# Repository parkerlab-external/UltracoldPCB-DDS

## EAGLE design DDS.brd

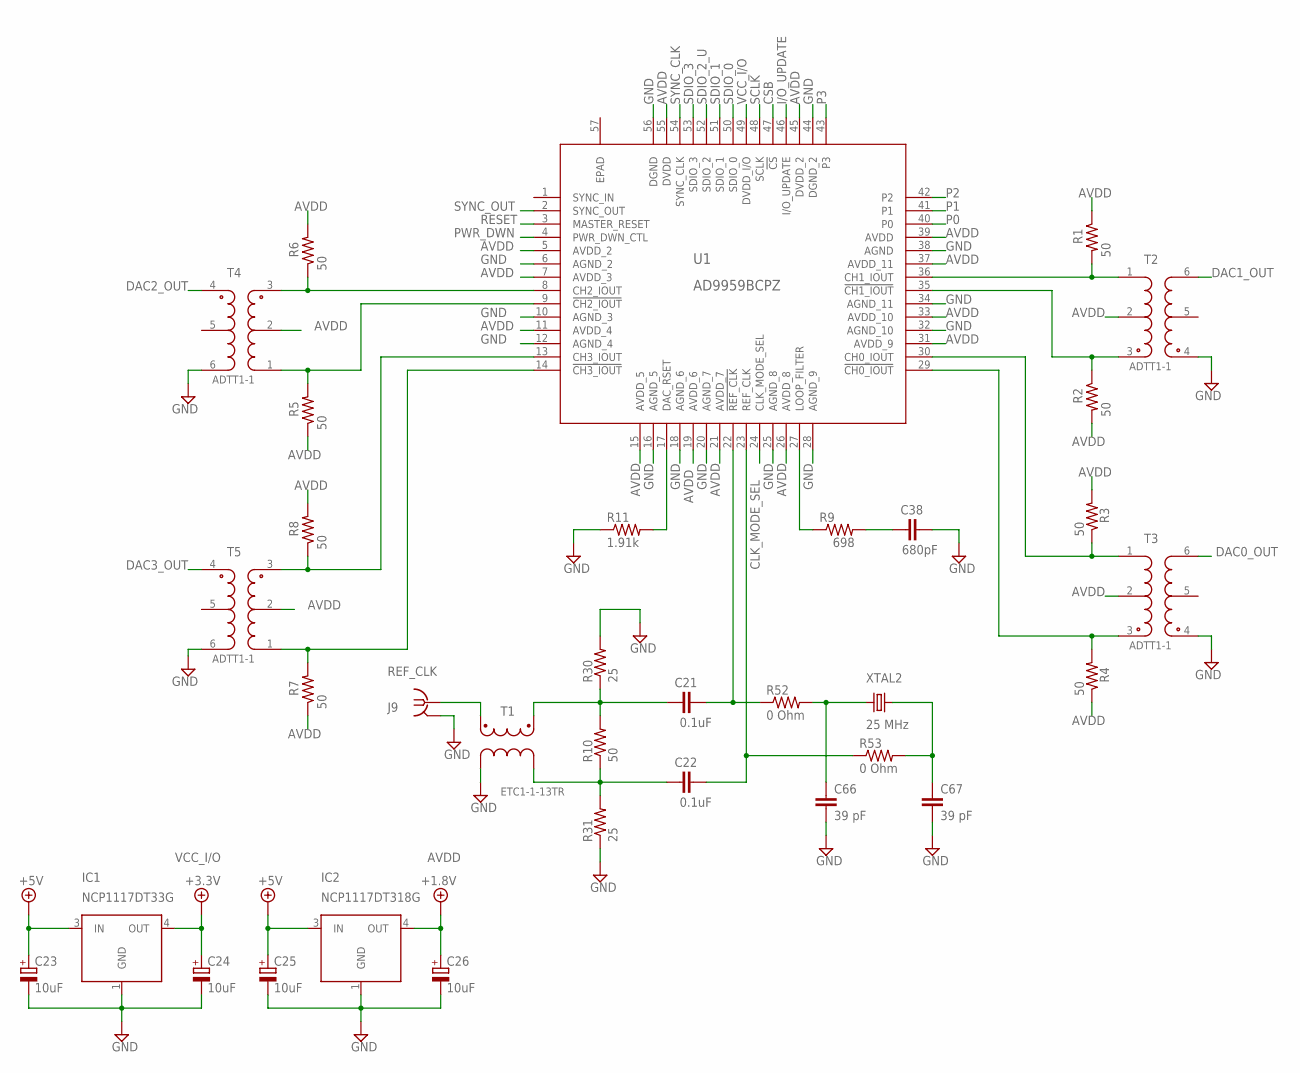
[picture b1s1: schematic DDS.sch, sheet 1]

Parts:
C21, C22: 0.1uF; C0402; MPN C0402C104K4RACTU
C23, C24, C25, C26: 10uF; CT3528; MPN T494B106K025AT
C38: 680pF; C0805; MPN MC0805N681J101CT
C66, C67: 39 pF; C0805; MPN MC0805N390J500CT
IC1: NCP1117DT33G; D-PAK_TO252AA; MPN NCP1117DT33G
IC2: NCP1117DT318G; D-PAK_TO252AA; MPN NCP1117DT18G
J9: REF_CLK; BU-SMA-V; MPN 142-0701-231
R1, R2, R3, R4, R5, R6, R7, R8, R10: 50; R0603; MPN CRCW060350R0FKEA
R9: 698; R0603; MPN ERJ-3EKF6980V
R11: 1.91k; R0603; MPN CRCW06031K91FKEA
R30, R31: 25; R0402; MPN NRC04F24R9TRF
R52, R53: 0 Ohm; R0402; MPN ERJ2GE0R00X
T1: ETC1-1-13TR; SM22
T2, T3, T4, T5: ADTT1-1; ADTT
U1: AD9959BCPZ; CP_56_1_ADI
XTAL2: 25 MHz; HC49UP

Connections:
+5V: C23.+, C25.+, IC1.3 (IN), IC2.3 (IN); also elsewhere on the board
AVDD: C26.+, IC2.4 (OUT), R1.1, R2.2, R3.2, R4.1, R5.1, R6.2, R7.1, R8.2, T2.2 (PRI0), T3.2 (PRI0), T4.2 (PRI0), T5.2 (PRI0), U1.5 (AVDD_2), U1.7 (AVDD_3), U1.11 (AVDD_4), U1.15 (AVDD_5), U1.19 (AVDD_6), U1.21 (AVDD_7), U1.26 (AVDD_8), U1.31 (AVDD_9), U1.33 (AVDD_10), U1.37 (AVDD_11), U1.39 (AVDD), U1.45 (DVDD_2), U1.55 (DVDD); also elsewhere on the board
CLK_MODE_SEL: U1.24 (CLK_MODE_SEL); also elsewhere on the board
CSB: U1.47 (!CS); also elsewhere on the board
DAC0_OUT: T3.6 (SEC-); also elsewhere on the board
DAC1_OUT: T2.6 (SEC-); also elsewhere on the board
DAC2_OUT: T4.4 (SEC+); also elsewhere on the board
DAC3_OUT: T5.4 (SEC+); also elsewhere on the board
GND: C23.-, C24.-, C25.-, C26.-, C38.2, C66.2, C67.2, IC1.1 (GND), IC2.1 (GND), J9.2 (GND), J9.3 (GND), J9.4 (GND), J9.5 (GND), R11.1, R30.2, R31.1, T1.4, T2.4 (SEC+), T3.4 (SEC+), T4.6 (SEC-), T5.6 (SEC-), U1.6 (AGND_2), U1.10 (AGND_3), U1.12 (AGND_4), U1.16 (AGND_5), U1.18 (AGND_6), U1.20 (AGND_7), U1.25 (AGND_8), U1.28 (AGND_9), U1.32 (AGND_10), U1.34 (AGND_11), U1.38 (AGND), U1.44 (DGND_2), U1.56 (DGND); also elsewhere on the board
I/O_UPDATE: U1.46 (I/O_UPDATE); also elsewhere on the board
unnamed: C21.1, R10.2, R30.1, T1.1
unnamed: R6.1, T4.3 (PRI+), U1.8 (CH2_IOUT)
unnamed: R5.2, T4.1 (PRI-), U1.9 (!CH2_IOUT)
unnamed: R4.2, T3.3 (PRI+), U1.29 (!CH0_IOUT)
unnamed: R1.2, T2.1 (PRI-), U1.36 (CH1_IOUT)
unnamed: R11.2, U1.17 (DAC_RSET)
unnamed: R9.1, U1.27 (LOOP_FILTER)
unnamed: C38.1, R9.2
unnamed: R7.2, T5.1 (PRI-), U1.14 (!CH3_IOUT)
unnamed: C66.1, R52.2, XTAL2.1
unnamed: R3.1, T3.1 (PRI-), U1.30 (CH0_IOUT)
unnamed: C67.1, R53.2, XTAL2.2
unnamed: C21.2, R52.1, U1.22 (!REF_CLK)
unnamed: C22.1, R10.1, R31.2, T1.3
unnamed: J9.1, T1.5
unnamed: C22.2, R53.1, U1.23 (REF_CLK)
unnamed: R8.1, T5.3 (PRI+), U1.13 (CH3_IOUT)
unnamed: R2.1, T2.3 (PRI+), U1.35 (!CH1_IOUT)
P0: U1.40 (P0); also elsewhere on the board
P1: U1.41 (P1); also elsewhere on the board
P2: U1.42 (P2); also elsewhere on the board
P3: U1.43 (P3); also elsewhere on the board
PWR_DWN: U1.4 (PWR_DWN_CTL); also elsewhere on the board
RESET: U1.3 (MASTER_RESET); also elsewhere on the board
SCLK: U1.48 (SCLK); also elsewhere on the board
SDIO_0: U1.50 (SDIO_0); also elsewhere on the board
SDIO_1: U1.51 (SDIO_1); also elsewhere on the board
SDIO_2_U: U1.52 (SDIO_2); also elsewhere on the board
SDIO_3: U1.53 (SDIO_3); also elsewhere on the board
SYNC_CLK: U1.54 (SYNC_CLK)
SYNC_OUT: U1.2 (SYNC_OUT)
VCC_I/O: C24.+, IC1.4 (OUT), U1.49 (DVDD_I/O); also elsewhere on the board

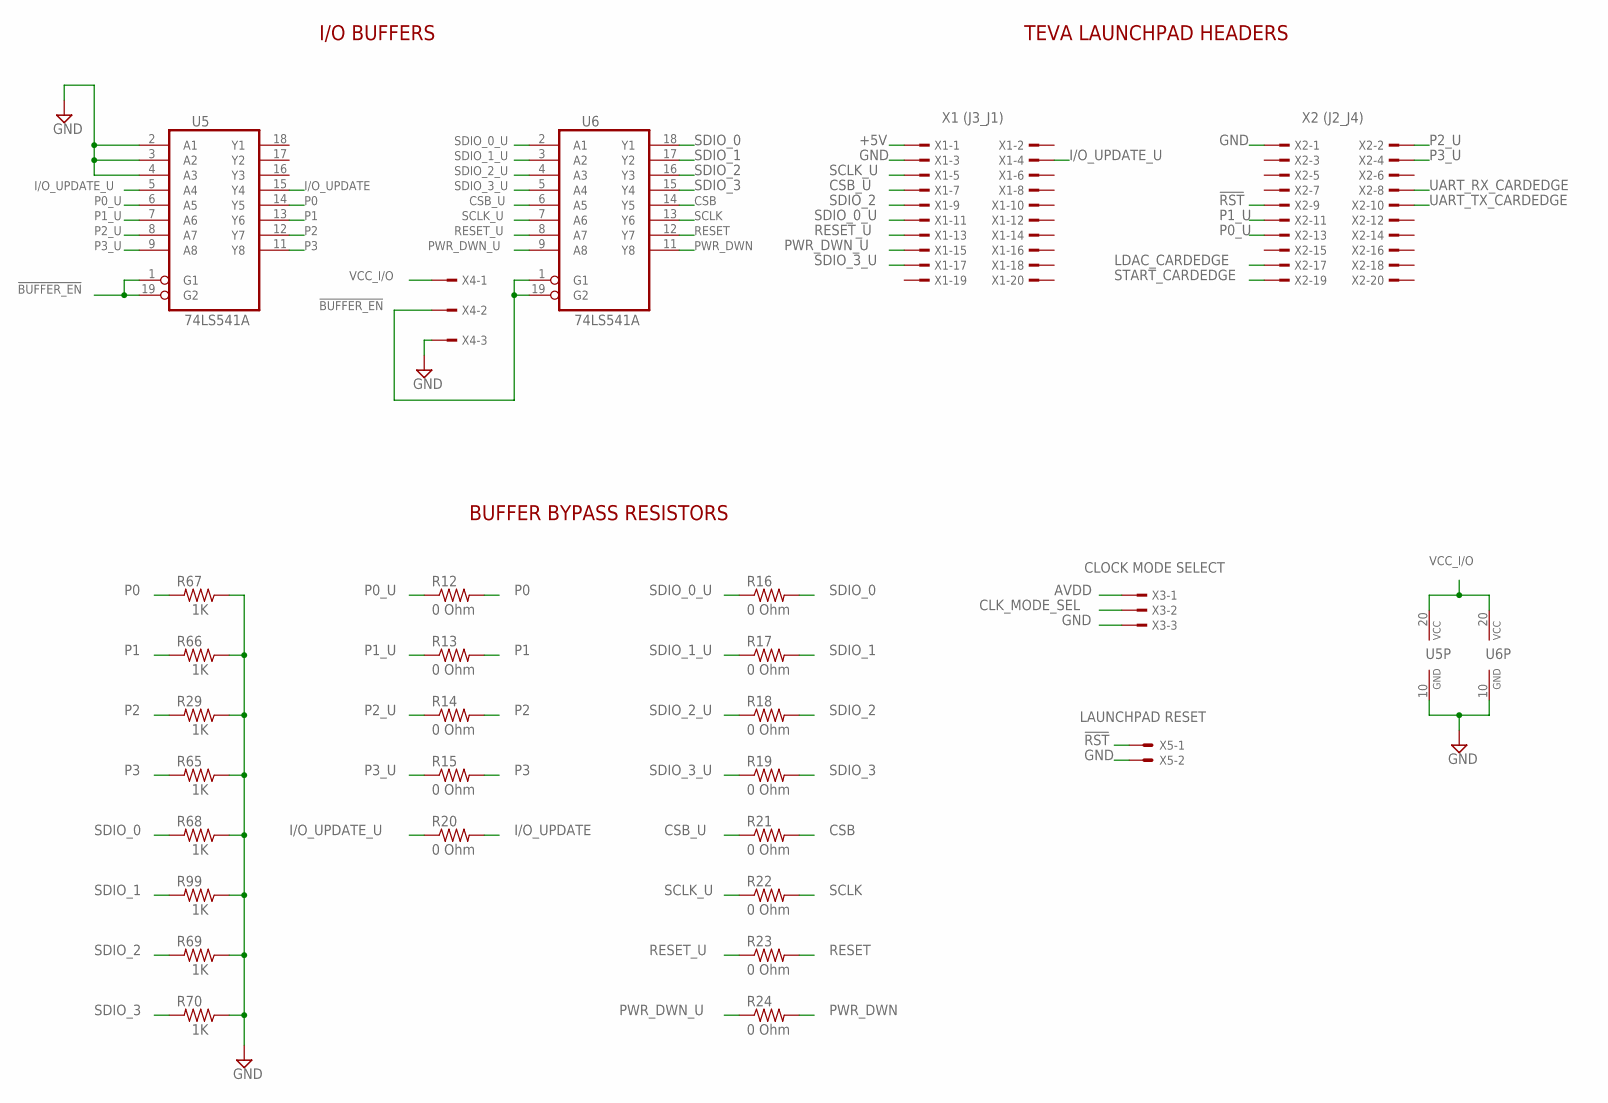
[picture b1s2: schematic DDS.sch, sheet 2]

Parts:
R12, R13, R14, R15, R16, R17, R18, R19, R20, R21, R22, R23, R24: 0 Ohm; R0402; MPN ERJ2GE0R00X
R29, R65, R66, R67, R68, R69, R70, R99: 1K; R0603; MPN ERJ-3EKF1001V
U5, U6: 74LS541A; SO20W; MPN SN74LVC541APW
X1: X1 (J3_J1); TSW-110-XX-G-D
X2: X2 (J2_J4); TSW-110-XX-G-D
X3: CLOCK MODE SELECT; TSW-103-XX-G-S
X4: BUFFER; TSW-103-XX-G-S
X5: LAUNCHPAD RESET; 22-23-2021

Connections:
!BUFFER_EN: U5.1 (G1), U5.19 (G2), U6.1 (G1), U6.19 (G2), X4.2
!RST: X2.9, X5.1
+5V: X1.1; also elsewhere on the board
AVDD: X3.1; also elsewhere on the board
CLK_MODE_SEL: X3.2; also elsewhere on the board
CSB: R21.2, U6.14 (Y5); also elsewhere on the board
CSB_U: R21.1, U6.6 (A5), X1.7
GND: R29.1, R65.1, R66.1, R67.1, R68.1, R69.1, R70.1, R99.1, U5.2 (A1), U5.3 (A2), U5.4 (A3), U5.10 (GND), U6.10 (GND), X1.3, X2.1, X3.3, X4.3, X5.2; also elsewhere on the board
I/O_UPDATE: R20.2, U5.15 (Y4); also elsewhere on the board
I/O_UPDATE_U: R20.1, U5.5 (A4), X1.4
LDAC_CARDEDGE: X2.17
P0: R12.2, R67.2, U5.14 (Y5); also elsewhere on the board
P0_U: R12.1, U5.6 (A5), X2.13
P1: R13.2, R66.2, U5.13 (Y6); also elsewhere on the board
P1_U: R13.1, U5.7 (A6), X2.11
P2: R14.2, R29.2, U5.12 (Y7); also elsewhere on the board
P2_U: R14.1, U5.8 (A7), X2.2
P3: R15.2, R65.2, U5.11 (Y8); also elsewhere on the board
P3_U: R15.1, U5.9 (A8), X2.4
PWR_DWN: R24.2, U6.11 (Y8); also elsewhere on the board
PWR_DWN_U: R24.1, U6.9 (A8), X1.15
RESET: R23.2, U6.12 (Y7); also elsewhere on the board
RESET_U: R23.1, U6.8 (A7), X1.13
SCLK: R22.2, U6.13 (Y6); also elsewhere on the board
SCLK_U: R22.1, U6.7 (A6), X1.5
SDIO_0: R16.2, R68.2, U6.18 (Y1); also elsewhere on the board
SDIO_0_U: R16.1, U6.2 (A1), X1.11
SDIO_1: R17.2, R99.2, U6.17 (Y2); also elsewhere on the board
SDIO_1_U: R17.1, U6.3 (A2)
SDIO_2: R18.2, R69.2, U6.16 (Y3), X1.9
SDIO_2_U: R18.1, U6.4 (A3); also elsewhere on the board
SDIO_3: R19.2, R70.2, U6.15 (Y4); also elsewhere on the board
SDIO_3_U: R19.1, U6.5 (A4), X1.17
START_CARDEDGE: X2.19
UART_RX_CARDEDGE: X2.8
UART_TX_CARDEDGE: X2.10
VCC_I/O: U5.20 (VCC), U6.20 (VCC), X4.1; also elsewhere on the board

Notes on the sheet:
I/O BUFFERS
TEVA LAUNCHPAD HEADERS
BUFFER BYPASS RESISTORS

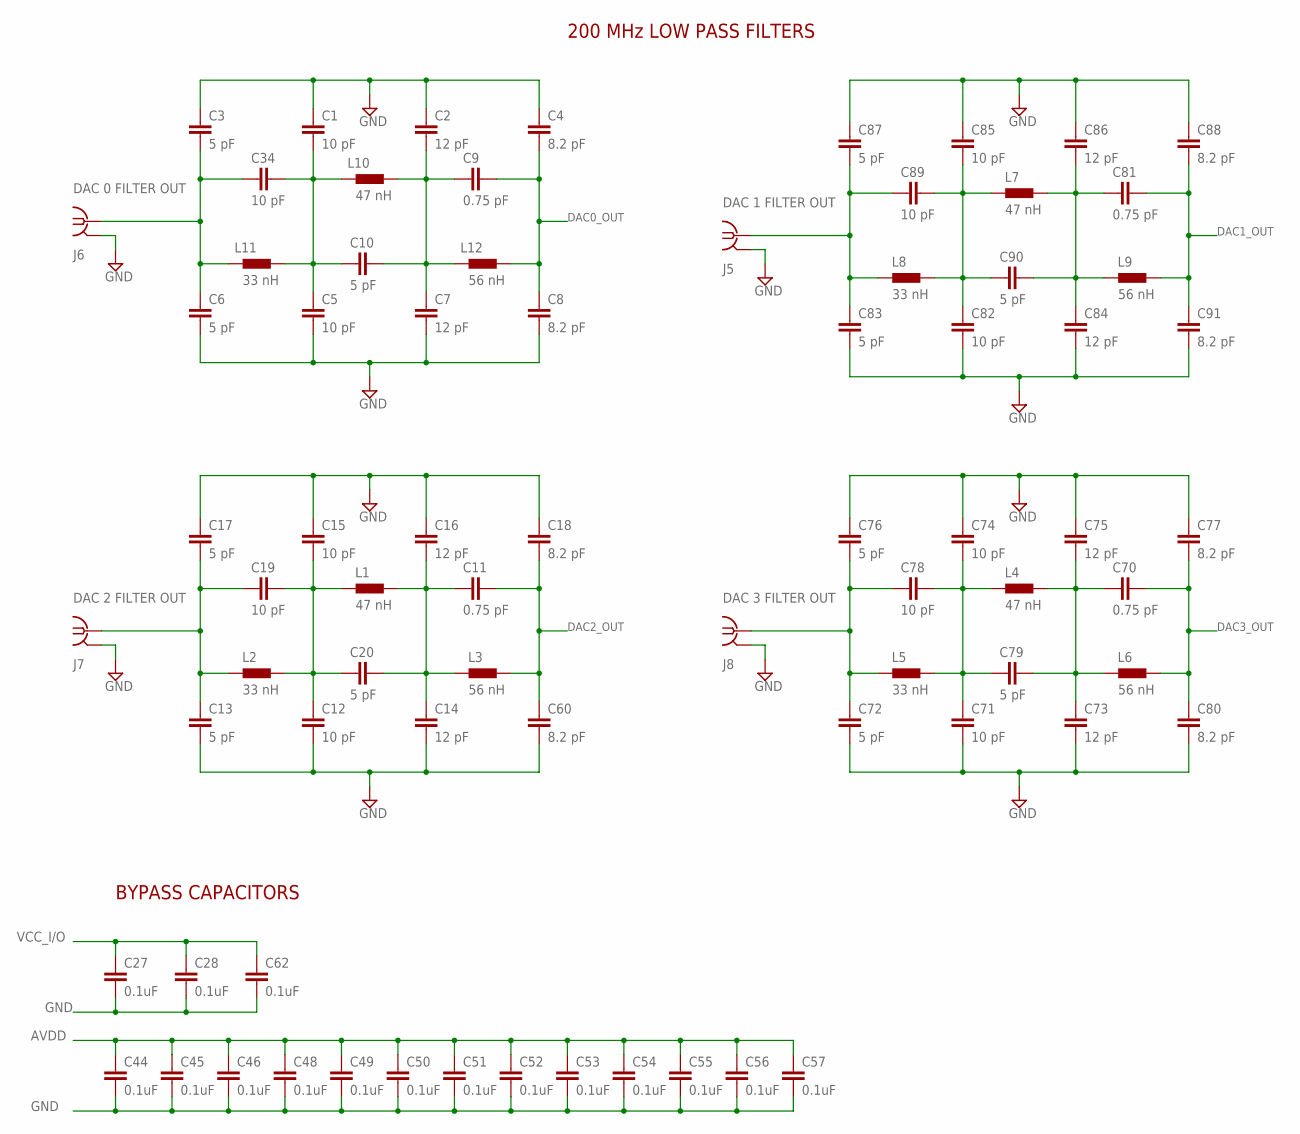
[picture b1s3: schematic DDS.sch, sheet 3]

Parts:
C1, C5, C12, C15, C19, C34, C71, C74, C78, C82, C85, C89: 10 pF; C0402; MPN CL05C100JB5NNNC
C2, C7, C14, C16, C73, C75, C84, C86: 12 pF; C0402; MPN 04025A120JAT2A
C3, C6, C10, C13, C17, C20, C72, C76, C79, C83, C87, C90: 5 pF; C0402; MPN GJM1555C1H5R0CB01D
C4, C8, C18, C60, C77, C80, C88, C91: 8.2 pF; C0402; MPN 04025A8R2BAT2A
C9, C11, C70, C81: 0.75 pF; C0402; MPN GJM1555C1HR75BB01D
C27, C28: 0.1uF; C0603; MPN 06035C104KAT2A
C44, C45, C46, C48, C49, C50, C51, C52, C53, C54, C55, C56, C57, C62: 0.1uF; C0402; MPN C0402C104K4RACTU
J5: DAC 1 FILTER OUT; BU-SMA-V; MPN 142-0701-231
J6: DAC 0 FILTER OUT; BU-SMA-V; MPN 142-0701-231
J7: DAC 2 FILTER OUT; BU-SMA-V; MPN 142-0701-231
J8: DAC 3 FILTER OUT; BU-SMA-V; MPN 142-0701-231
L1, L4, L7, L10: 47 nH; 0402; MPN LQG15HN47NJ02D
L2, L5, L8, L11: 33 nH; 0402; MPN LQG15HS33NJ02D
L3, L6, L9, L12: 56 nH; 0402; MPN LQG15HS56NJ02D

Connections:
AVDD: C44.1, C45.1, C46.1, C48.1, C49.1, C50.1, C51.1, C52.1, C53.1, C54.1, C55.1, C56.1, C57.1; also elsewhere on the board
DAC0_OUT: C4.2, C8.1, C9.1, L12.2; also elsewhere on the board
DAC1_OUT: C81.1, C88.2, C91.1, L9.2; also elsewhere on the board
DAC2_OUT: C11.1, C18.2, C60.1, L3.2; also elsewhere on the board
DAC3_OUT: C70.1, C77.2, C80.1, L6.2; also elsewhere on the board
GND: C1.1, C2.1, C3.1, C4.1, C5.2, C6.2, C7.2, C8.2, C12.2, C13.2, C14.2, C15.1, C16.1, C17.1, C18.1, C27.2, C28.2, C44.2, C45.2, C46.2, C48.2, C49.2, C50.2, C51.2, C52.2, C53.2, C54.2, C55.2, C56.2, C57.2, C60.2, C62.2, C71.2, C72.2, C73.2, C74.1, C75.1, C76.1, C77.1, C80.2, C82.2, C83.2, C84.2, C85.1, C86.1, C87.1, C88.1, C91.2, J5.2 (GND), J5.3 (GND), J5.4 (GND), J5.5 (GND), J6.2 (GND), J6.3 (GND), J6.4 (GND), J6.5 (GND), J7.2 (GND), J7.3 (GND), J7.4 (GND), J7.5 (GND), J8.2 (GND), J8.3 (GND), J8.4 (GND), J8.5 (GND); also elsewhere on the board
unnamed: C81.2, C84.1, C86.2, C90.1, L7.2, L9.1
unnamed: C83.1, C87.2, C89.2, J5.1, L8.1
unnamed: C82.1, C85.2, C89.1, C90.2, L7.1, L8.2
unnamed: C13.1, C17.2, C19.2, J7.1, L2.1
unnamed: C2.2, C7.1, C9.2, C10.1, L10.2, L12.1
unnamed: C3.2, C6.1, C34.2, J6.1, L11.1
unnamed: C1.2, C5.1, C10.2, C34.1, L10.1, L11.2
unnamed: C11.2, C14.1, C16.2, C20.1, L1.2, L3.1
unnamed: C12.1, C15.2, C19.1, C20.2, L1.1, L2.2
unnamed: C70.2, C73.1, C75.2, C79.1, L4.2, L6.1
unnamed: C72.1, C76.2, C78.2, J8.1, L5.1
unnamed: C71.1, C74.2, C78.1, C79.2, L4.1, L5.2
VCC_I/O: C27.1, C28.1, C62.1; also elsewhere on the board

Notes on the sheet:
200 MHz LOW PASS FILTERS
BYPASS CAPACITORS

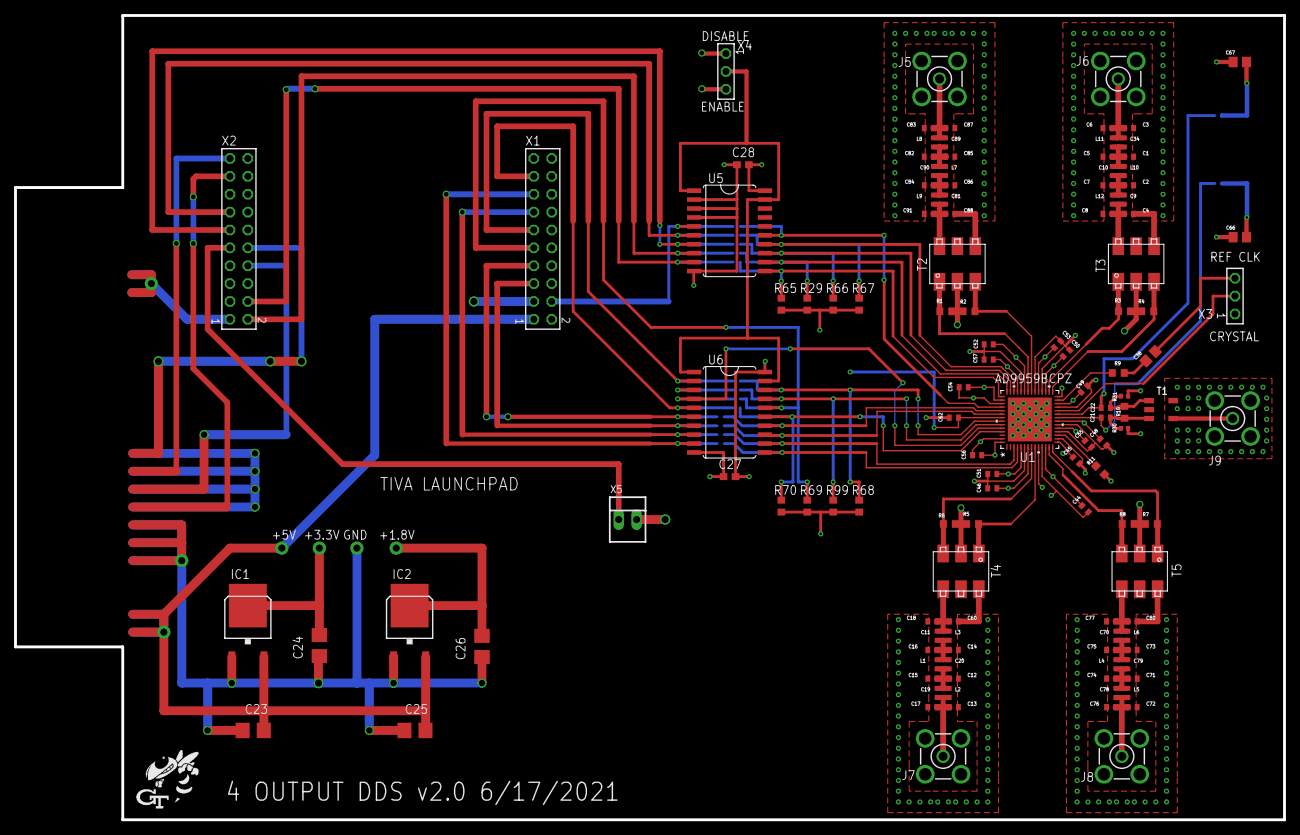
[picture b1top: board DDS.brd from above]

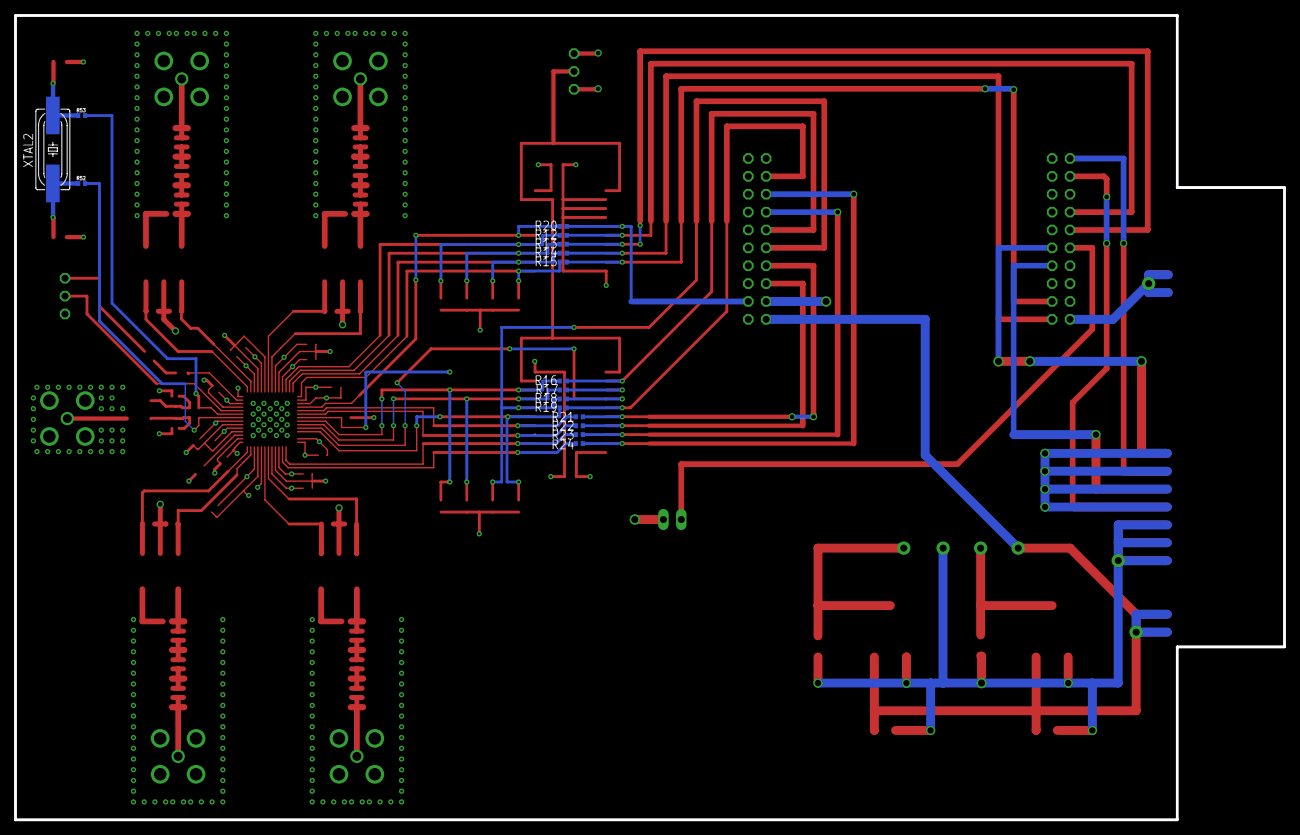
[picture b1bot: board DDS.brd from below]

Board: 4 copper layers, 180.3 x 114.3 mm, 138 parts (16 on the bottom side), 67 nets.

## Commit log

2025-03-03 Design files.
